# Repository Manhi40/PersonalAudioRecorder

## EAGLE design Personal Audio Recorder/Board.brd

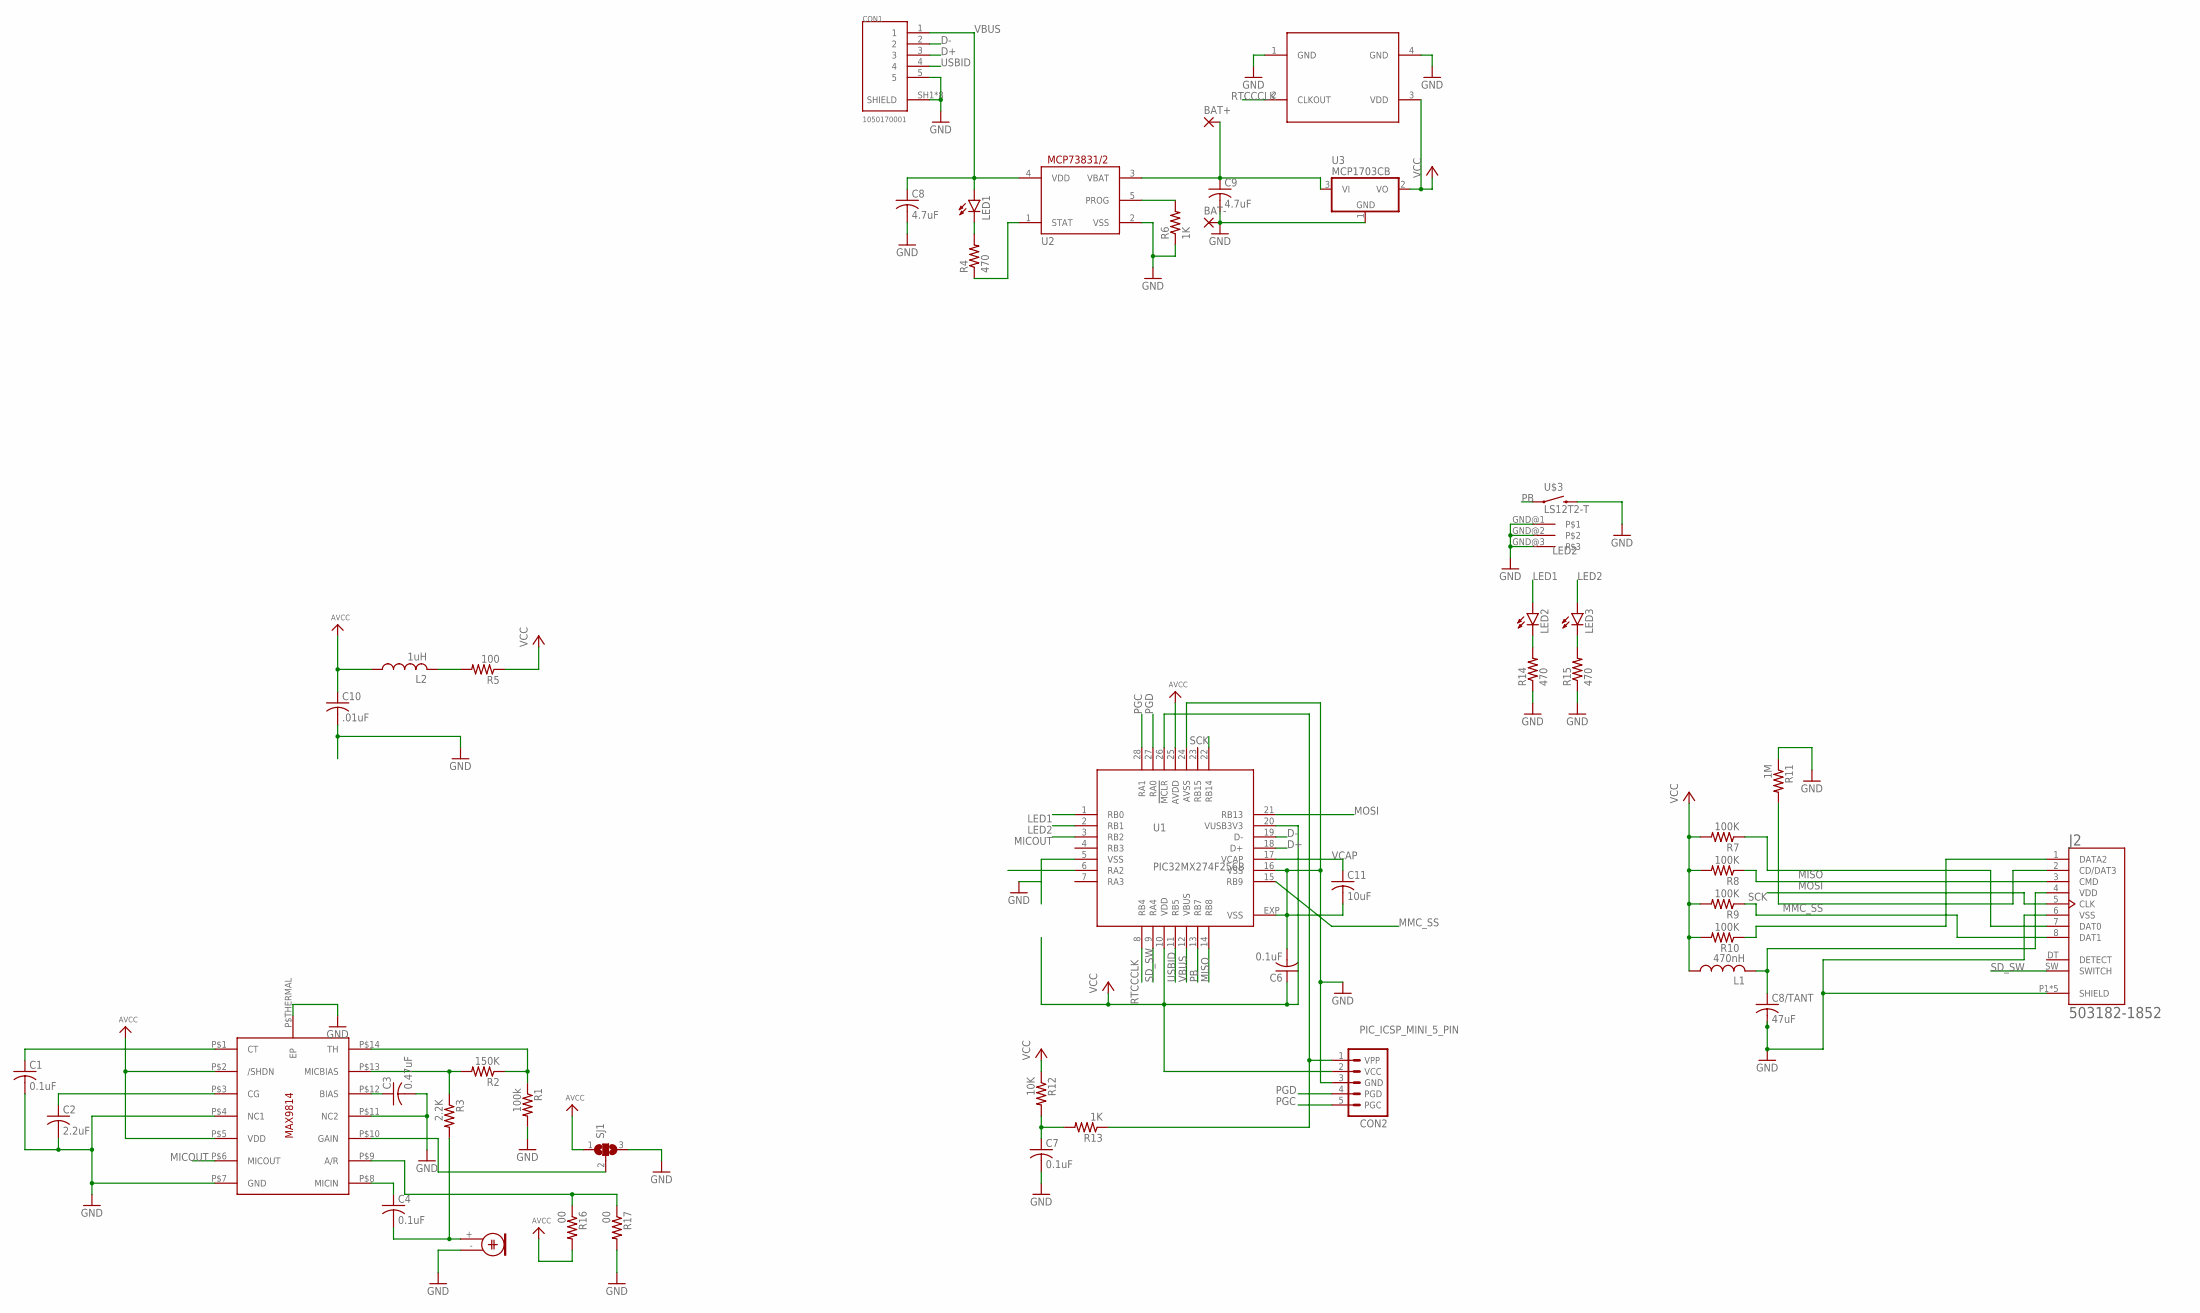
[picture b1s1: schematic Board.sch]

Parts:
BAT+: SMD2; SMD1,27-2,54
BAT-: SMD2; SMD1,27-2,54
C1, C4, C6, C7: 0.1uF; C0603
C2: 2.2uF; C0603
C3: 0.47uF; C0603
C8, C9: 4.7uF; C0603
C8/TANT: 47uF; C0805
C10: .01uF; C0603
C11: 10uF; C0603
CON1: 1050170001; MOLEX_1050170001
CON2: PIC_ICSP_MINI_5_PIN
J2: 503182-1852; MOLEX_503182-1852
L1: 470nH; L2012C
L2: 1uH; L2012C
LED1, LED2, LED3: LEDCHIP-LED0805; CHIP-LED0805
MIC: ELECTRET; 9.7ELECTRET
R1: 100k; R0603
R2: 150K; R0603
R3: 2.2K; R0603
R4, R14, R15: 470; R0603
R5: 100; R0603
R6, R13: 1K; R0603
R7, R8, R9, R10: 100K; R0603
R11: 1M; R0603
R12: 10K; R0603
R16, R17: 00; R0603
SJ1: SJ2WJUMPER; C0R-JMP
U1: PIC32MX274F256B; QFN28-ML_6X6MM
U2: MCP73831/OT; SOT23-5L
U3: MCP1703CB; SOT23
U4: MAX9814TDFN14; TDFN14_3X3MM
U$3: LS12T2-T
X1: SIT1532AC-J5-DCC; 4-UFBGA

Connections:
AVCC: C10.1, L2.1, R16.2, SJ1.1, U1.25 (AVDD), U4.P$2 (/SHDN), U4.P$5 (VDD)
D+: CON1.3, U1.18 (D+)
D-: CON1.2, U1.19 (D-)
GND: BAT-.1, C1.2, C2.2, C3.2, C6.2, C7.2, C8.2, C8/TANT.2, C9.2, C10.2, C11.2, CON1.5, CON1.SH1 (SHIELD), CON1.SH2 (SHIELD), CON1.SH3 (SHIELD), CON1.SH4 (SHIELD), CON1.SH5 (SHIELD), CON1.SH6 (SHIELD), CON1.SH7 (SHIELD), CON1.SH8 (SHIELD), CON2.3 (GND), J2.6 (VSS), J2.P1 (SHIELD), J2.P2 (SHIELD), J2.P3 (SHIELD), J2.P4 (SHIELD), J2.P5 (SHIELD), MIC.- (1), R1.2, R6.1, R11.1, R14.1, R15.1, R17.2, SJ1.3, U1.5 (VSS), U1.16 (VSS), U1.24 (AVSS), U1.EXP (VSS), U2.2 (VSS), U3.1 (GND), U4.P$4 (NC1), U4.P$7 (GND), U4.P$11 (NC2), U4.P$THERMAL (EP), U$3.GND@1, U$3.GND@2, U$3.GND@3, U$3.S2 (2), X1.1 (GND), X1.4 (GND)
LED1: LED2.A, U1.1 (RB0)
LED2: LED3.A, U1.2 (RB1)
MICOUT: U1.3 (RB2), U4.P$6 (MICOUT)
MISO: J2.7 (DAT0), R7.1, U1.14 (RB8)
MMC_SS: J2.2 (CD/DAT3), R11.2, U1.15 (RB9)
MOSI: J2.3 (CMD), R8.1, U1.21 (RB13)
unnamed: C1.1, U4.P$1 (CT)
unnamed: C2.1, U4.P$3 (CG)
unnamed: R2.2, R3.1, U4.P$13 (MICBIAS)
unnamed: R16.1, R17.1, U4.P$9 (A/R)
unnamed: J2.1 (DATA2), R10.1
unnamed: R1.1, R2.1, U4.P$14 (TH)
unnamed: J2.8 (DAT1), R9.1
unnamed: C4.2, MIC.+ (2), R3.2
unnamed: LED1.C, R4.2
unnamed: R4.1, U2.1 (STAT)
unnamed: C7.1, R12.2, R13.2
unnamed: R6.2, U2.5 (PROG)
unnamed: CON2.1 (VPP), R13.1, U1.26 (!MCLR)
unnamed: C3.1, U4.P$12 (BIAS)
unnamed: BAT+.1, C9.1, U2.3 (VBAT), U3.3 (VI)
unnamed: LED2.C, R14.2
unnamed: LED3.C, R15.2
unnamed: C8/TANT.1, J2.4 (VDD), L1.2
unnamed: C4.1, U4.P$8 (MICIN)
unnamed: L2.2, R5.2
unnamed: SJ1.2, U4.P$10 (GAIN)
PB: U1.13 (RB7), U$3.S1 (1)
PGC: CON2.5 (PGC), U1.28 (RA1)
PGD: CON2.4 (PGD), U1.27 (RA0)
RTCCCLK: U1.8 (RB4), X1.2 (CLKOUT)
SCK: J2.5 (CLK), U1.22 (RB14)
SD_SW: J2.SW (SWITCH), U1.9 (RA4)
USBID: CON1.4, U1.11 (RB5)
VBUS: C8.1, CON1.1, LED1.A, U1.12 (VBUS), U2.4 (VDD)
VCAP: C11.1, U1.17 (VCAP)
VCC: C6.1, CON2.2 (VCC), L1.1, R5.1, R7.2, R8.2, R9.2, R10.2, R12.1, U1.10 (VDD), U1.20 (VUSB3V3), U3.2 (VO), X1.3 (VDD)

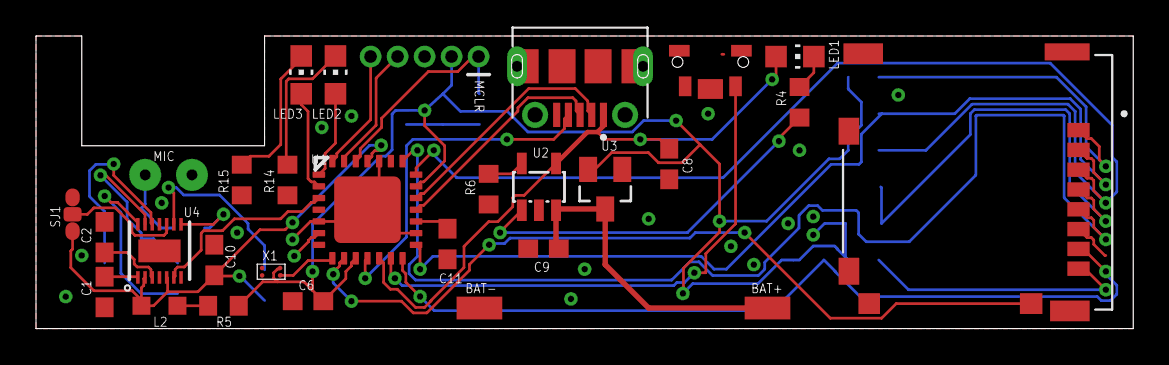
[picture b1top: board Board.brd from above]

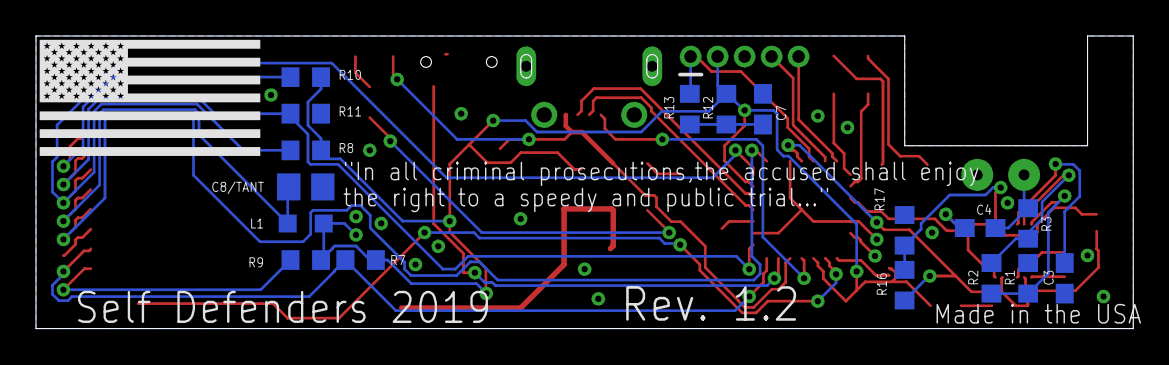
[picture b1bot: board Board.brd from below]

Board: 2 copper layers, 61.0 x 16.3 mm, 46 parts (17 on the bottom side), 41 nets.

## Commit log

2018-11-24 Initial code added
2018-11-27 Almost working sampling code.
2018-11-27 Nightly commit
2018-12-07 Functional audio recording Sounds not bad
2019-01-05 Added EAGLECAD files for PCB
2019-01-06 Changed MCU
2019-01-12 Changed chip, complete rehaul
2019-02-19 Fixed SD card issue, Recording works on new board
2019-02-21 DMA implemented, audio recording rate set to 37500ish
2019-02-26 Started to implement codec
2019-02-28 Redid board
2019-03-07 Added untested code for audio encoding
2019-03-07 Added more encoding code, added file splitting
2019-03-15 PCB update
2019-03-24 Rev 1.2 board done and sent off
2019-04-02 Encoding now works, 32MB wav files are written to the SD card
2019-04-03 Trying to merge...
2019-04-03 Fixed problems after merge
2019-04-03 Changed harmony config
2019-04-15 Recording works properly on new board, output is a functioning .wav file
2019-05-03 Works...

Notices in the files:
parts and their libraries:
SparkFun-Connectors: Licensing: Creative Commons ShareAlike 4.0 International - https://creativecommons.org/licenses/by-sa/4.0
microbuilder: This work is placed in the public domain, and may be freely used for commercial and non-commercial work with the following conditions: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
